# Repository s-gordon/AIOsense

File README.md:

# AIOsense

## Description
Based on the idea of an all-in-one sensor AIOsense was born.

The goal is to provide you with a sensor that is modular, affordable and
easy to solder (no SMD) as an alternative for commercially available sensors. We
also focus on upgrade-ability, so you don't have to buy all parts again in case
of a new PCB release. In most cases, this sensor is cheaper and better than the
commercially ones. 

## Available Sensors / Modules

- (RGB)-LED
- Barometer
- Breath VOC equivalent
- Buzzer / Beeper
- CO² equivalent
- Humidity sensor
- Light / Illumination sensor
- Microphone
- PIR motion sensor
- Speaker
- Temperature sensor
- Voice Assistant (ESP32-S2 / S3 only)
- mmWave / Radar sensor

All supported sensors & modules are listed in the documentation:
[Sensor Modules](https://aiosense.readthedocs.io/en/latest/sensors/)

## What does it look like? 👀

| Without lid                        | With lid                             |
|------------------------------------|--------------------------------------|
|  |  |

> **Note:** The PCB in this image is not fully equipped either is this the final case
> design ([issue](https://github.com/Schluggi/AIOsense/issues/9)).

### Rendered images

| 3D                          | 2D                       |
|-----------------------------|--------------------------|
|  |  |

### Schematic

You can find the schematic [here](schematic/AIOsense.pdf).

## Power consumption

The power consumption depends on your configuration. On a fully equipped Board (ESP32-C3 + mmWave + PIR + BME280 +
LightSensor) we measured an idle power consumption of **0.45W / 0.09A** some peaks around **0.78W / 0.15A**.

Without a mmWave sensor the idle power consumption is around **0.11W / 0.02A** and peak near **0.45W / 0.09A**.

## How to start

You want to make your own AIOsense?<br>
Let's jump right into the [documentation](https://aiosense.readthedocs.io/en/latest/quickstart/).

## Questions?

Just open an [issue](https://github.com/Schluggi/AIOsense/issues/new) :)

## Credits & Special thanks

Created and maintained by Lukas Schulte-Tickmann / [Schluggi](https://github.com/Schluggi).

### Special thanks
- My dad for some electrical engineering advice and PCB reviewing
- [lukas-holzner](https://github.com/lukas-holzner) for the case design and some general discussions about the board
- [jankae](https://github.com/jankae) for PCB reviewing
- [reschandreas](https://github.com/reschandreas) for general repo work
- [PCBWay³](https://pcbway.com/g/DFb536) for sponsoring the PCB prototypes

### Contributors

<br>

Inspired by [EverythingSmartHome](https://everythingsmarthome.co.uk/).

<hr>
³ Affiliate link

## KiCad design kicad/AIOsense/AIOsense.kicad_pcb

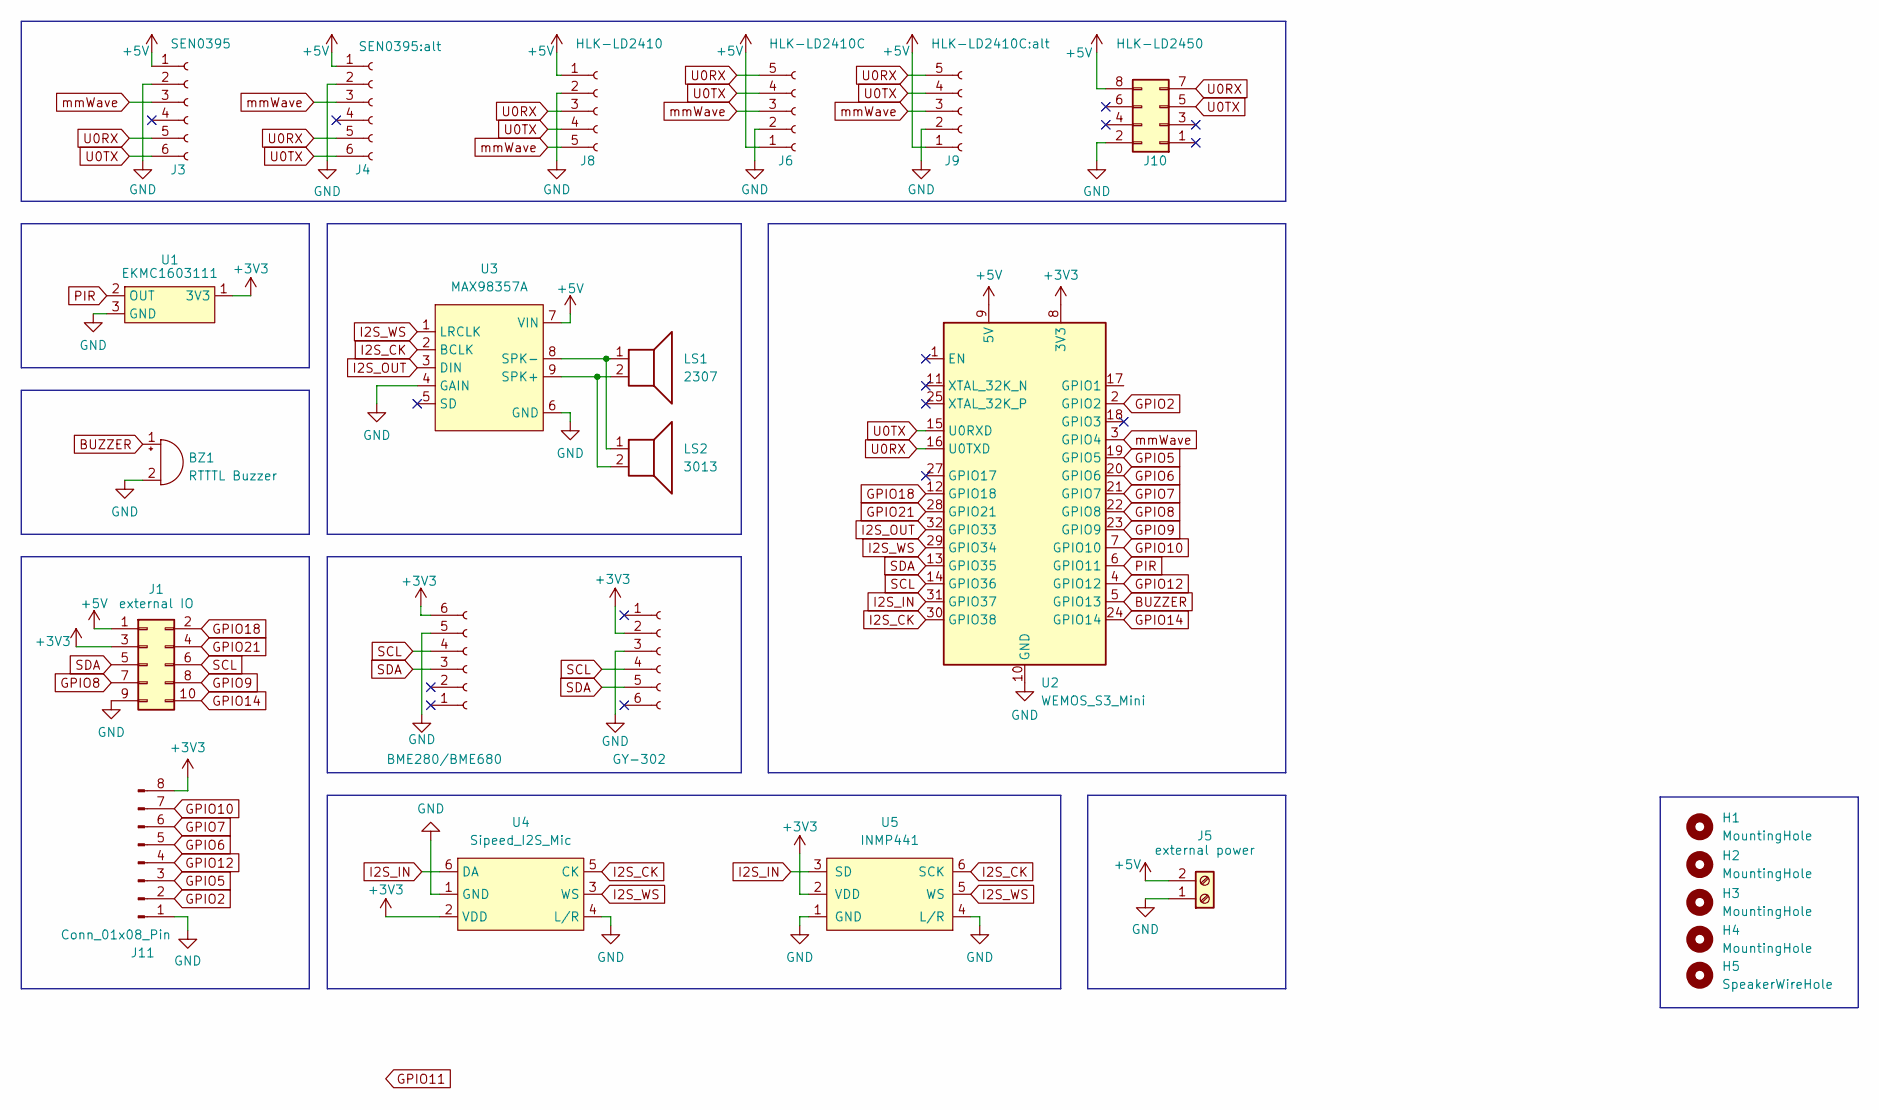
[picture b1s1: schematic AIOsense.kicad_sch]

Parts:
BZ1: RTTTL Buzzer; Buzzer_D12mm_P6.5mm
H1, H2, H3, H4: MountingHole; MountingHole_3.2mm_M3_DIN965_Pad
H5: SpeakerWireHole; Hole_Unplated_3.0mm
J1: external IO; PinHeader_2x05_P2.54mm_Vertical
J2: GY-302; PinSocket_1x06_P2.54mm_Vertical
J3: SEN0395; PinSocket_1x06_P2.54mm_Vertical; Manufacturer_Part_Number SEN0395; Digikey Part # 1738-SEN0395-ND
J4: SEN0395:alt; PinSocket_1x06_P2.54mm_Vertical; Manufacturer_Part_Number SEN0395; Digikey Part # 1738-SEN0395-ND
J5: external power; TerminalBlock_TE_282834-2_1x02_P2.54mm_Horizontal; Manufacturer_Part_Number 691210910002; Digikey Part # 732-691210910002-ND
J6: HLK-LD2410C; PinSocket_1x05_P2.54mm_Vertical; Manufacturer_Part_Number LD2410; Digikey Part # /
J7: BME280/BME680; PinSocket_1x06_P2.54mm_Vertical
J8: HLK-LD2410; PinSocket_1x05_P1.27mm_Vertical; Manufacturer_Part_Number LD2410; Digikey Part # /
J9: HLK-LD2410C:alt; PinSocket_1x05_P2.54mm_Vertical; Manufacturer_Part_Number LD2410; Digikey Part # /
J10: HLK-LD2450; PinSocket_2x04_P2.00mm_Vertical
J11: Conn_01x08_Pin; PinHeader_1x08_P2.54mm_Vertical
LS1: 2307; Speaker_2307
LS2: 3013; Speaker_3013
U1: EKMC1603111; PIR_EKMC1603111_TO-5; Manufacturer_Part_Number EKMC1603111; Digikey Part # 255-3086-ND
U2: WEMOS_S3_Mini
U3: MAX98357A; Adafruit_MAX98357A
U4: Sipeed_I2S_Mic
U5: INMP441; Manufacturer_Part_Number INMP441ACEZ-R7; Digikey Part # obsolete

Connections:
+3V3: J1.3, J2.2, J7.6, J11.8, U1.1 (3V3), U2.8 (3V3), U4.2 (VDD), U5.2 (VDD)
+5V: J1.1, J3.1, J4.1, J5.2, J6.1, J8.1, J9.1, J10.8, U2.9 (5V), U3.7 (VIN)
BUZZER: BZ1.1 (-), U2.5 (GPIO13)
GND: BZ1.2 (+), J1.9, J2.3, J3.2, J4.2, J5.1, J6.2, J7.5, J8.2, J9.2, J10.2, J11.1, U1.3 (GND), U2.10 (GND), U2.26 (GND), U3.4 (GAIN), U3.6 (GND), U4.1 (GND), U4.4 (L/R), U5.1 (GND), U5.4 (L/R)
GPIO2: J11.2, U2.2 (GPIO2)
GPIO5: J11.3, U2.19 (GPIO5)
GPIO6: J11.5, U2.20 (GPIO6)
GPIO7: J11.6, U2.21 (GPIO7)
GPIO8: J1.7, U2.22 (GPIO8)
GPIO9: J1.8, U2.23 (GPIO9)
GPIO10: J11.7, U2.7 (GPIO10)
GPIO12: J11.4, U2.4 (GPIO12)
GPIO14: J1.10, U2.24 (GPIO14)
GPIO18: J1.2, U2.12 (GPIO18)
GPIO21: J1.4, U2.28 (GPIO21)
I2S_CK: U2.30 (GPIO38), U3.2 (BCLK), U4.5 (CK), U5.6 (SCK)
I2S_IN: U2.31 (GPIO37), U4.6 (DA), U5.3 (SD)
I2S_OUT: U2.32 (GPIO33), U3.3 (DIN)
I2S_WS: U2.29 (GPIO34), U3.1 (LRCLK), U4.3 (WS), U5.5 (WS)
unnamed: LS1.2, LS2.2, U3.9 (SPK+)
unnamed: LS1.1, LS2.1, U3.8 (SPK-)
PIR: U1.2 (OUT), U2.6 (GPIO11)
SCL: J1.6, J2.4, J7.4, U2.14 (GPIO36)
SDA: J1.5, J2.5, J7.3, U2.13 (GPIO35)
U0RX: J3.5, J4.5, J6.5, J8.3, J9.5, J10.7, U2.16 (U0TXD)
U0TX: J3.6, J4.6, J6.4, J8.4, J9.4, J10.5, U2.15 (U0RXD)
mmWave: J3.3, J4.3, J6.3, J8.5, J9.3, U2.3 (GPIO4)

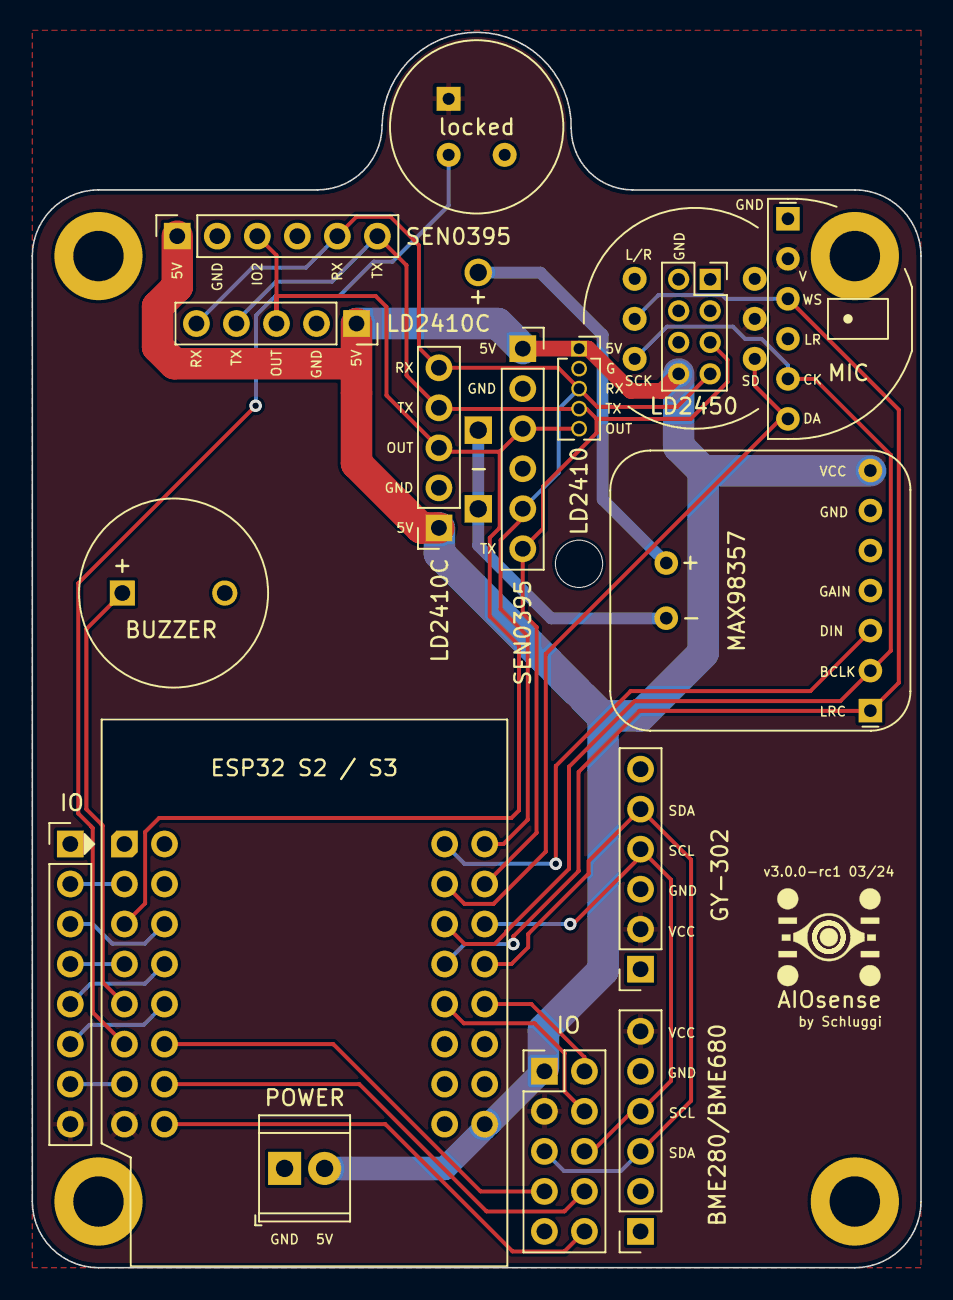
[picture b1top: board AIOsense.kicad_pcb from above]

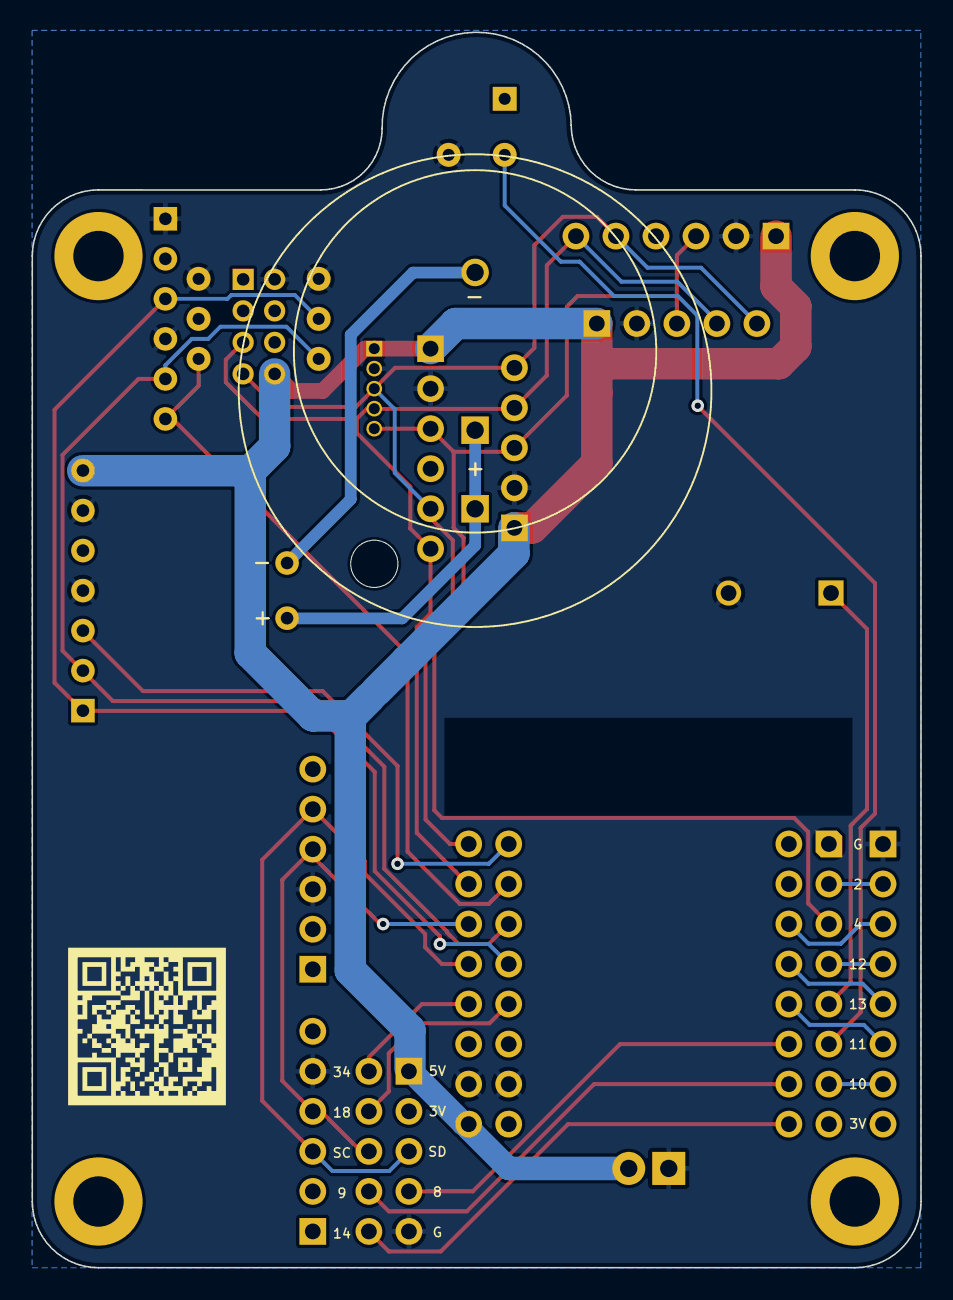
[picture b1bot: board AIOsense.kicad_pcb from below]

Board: 2 copper layers, 56.4 x 78.4 mm, 24 parts (2 on the bottom side), 27 nets.

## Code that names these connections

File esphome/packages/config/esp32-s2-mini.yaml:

substitutions:
  buzzer_pin: GPIO9
  i2s_bclk_pin: GPIO36    # SCK
  i2s_din_pin: GPIO38     # mic
  i2s_dout_pin: GPIO40    # speaker
  i2s_lrclk_pin: GPIO34   # WS
  led_pin: GPIO15
  pir_pin: GPIO11
  sen0395_io_pin: GPIO5
  uart_rx_pin: GPIO37
  uart_tx_pin: GPIO39

esp32:
  board: lolin_s2_mini
  flash_size: 4MB
  framework:
    type: esp-idf
    version: recommended

i2c:
  sda: GPIO33
  scl: GPIO35

sensor:
  - platform: internal_temperature
    name: "CPU Temperature"

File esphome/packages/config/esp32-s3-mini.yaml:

substitutions:
  buzzer_pin: GPIO13
  i2s_bclk_pin: GPIO38    # SCK
  i2s_din_pin: GPIO37     # mic
  i2s_dout_pin: GPIO33    # speaker
  i2s_lrclk_pin: GPIO34   # WS
  pir_pin: GPIO11
  rgb_led_pin: GPIO47
  rgb_led_type: RGB
  sen0395_io_pin: GPIO4
  uart_rx_pin: GPIO44
  uart_tx_pin: GPIO43

esp32:
  board: esp32-s3-devkitc-1
  variant: esp32s3
  flash_size: 4MB
  framework:
    type: esp-idf
    version: latest

i2c:
  sda: GPIO35
  scl: GPIO36
  frequency: 400kHz

sensor:
  - platform: internal_temperature
    name: "CPU Temperature"

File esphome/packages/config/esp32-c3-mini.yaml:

substitutions:
  buzzer_pin: A0
  i2s_bclk_pin: A1
  i2s_lrclk_pin: A5
  pir_pin: A4
  rgb_led_pin: GPIO7
  rgb_led_type: GRB
  sen0395_io_pin: A2
  uart_rx_pin: GPIO20
  uart_tx_pin: GPIO21

esphome:
  platformio_options:
    board_build.extra_flags:
      - "-DARDUINO_USB_CDC_ON_BOOT=0"
    board_build.flash_mode: dio

esp32:
  board: lolin_c3_mini
  flash_size: 4MB
  framework:
    type: esp-idf
    version: recommended

wifi:
  output_power: 8.5dBm

i2c:
  sda: GPIO8
  scl: GPIO10

sensor:
  - platform: internal_temperature
    name: "CPU Temperature"

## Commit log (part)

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2023-02-07 Added initial stls for case.
2023-02-07 Updated case. Light holes expanded for sensor. Made stand longer to allow clearance for USB cable. Lowered PIR sensor to proper height with TO-5 3 pin socket.
2025-01-15 Added draft VA to LED version
2025-01-15 disable led output
2025-01-15 Typo. Remove switch.is_on listen light condition for reset_led
2025-01-15 Corrected incorrect GPIO pin assignment for speaker and mic
2025-01-15 Increased trace width for amp terminals to speaker from 0.5 to 0.75 to decrease noise. Bridged GAIN to GND to increase gain from 9 dB to 12 dB
2025-01-15 Swapped GND and VDD on Sipeed mic for alt layout from vendor.
2025-01-22 Prelim updates to S3 config
2025-01-22 platform change from neopixelbus to esp32_rmt_led_strip
2025-01-22 Relaxed esp-idf version for s3
2025-01-22 Throttle LD2410
2025-01-22 Correct pin assignments for S3 mini
2025-01-22 Added speaker to VA and updated voice_assistant
2025-01-22 Remove smoothing window on BME280
2025-01-22 Added state classes
2025-01-23 Fixed esp32-s3 framework version
2025-01-23 voice assist (no-led and rgb)
2025-01-23 Removed temperature offset
2025-01-23 Removed "allow_other_uses"
2025-01-23 Brought down brightness of LED for voice assist
2025-01-24 Added vad
2025-01-24 Removed vad
2025-01-25 Added slow and fast pulse effects
2025-01-27 Added more control to switch off voice assist.
2025-01-29 Corrected renamed i2s_dout_pin for speaker.
2025-01-30 Removed obsolete boards.
2025-01-30 Updated pin assignments for rc1. Added i2s_dout_pin for amplifier/speaker.
2025-01-30 Added optional media_player sensor
2025-01-30 Added speaker to voice assist sensor. Renamed i2s component IDs to improve clarity.
2025-01-30 Removed use_wake_word switch
2025-01-30 Added wake_word_engine selector. Added micro_wake_word with alexa and hey_jarvis.
2025-01-31 Invert LED on C3 mini
2025-01-31 Corrected invert LED back and added arduino framework for C3
2025-01-31 Removed esp32 from media_player
2025-01-31 Added additional LED effects for media player announcements
2025-01-31 LED effects not supported on GPIO platform. Switched to monochromatic and ledc
2025-01-31 Update board for s2 and c3
2025-01-31 Enforce arduino frameword for media_player
2025-01-31 Switching framework in media_player is problematic
2025-01-31 Typo in platform name
2025-01-31 Added esp32 section back in to MP
2025-02-01 Added Fast Pulse and Slow Pulse light effects. Should also now set framework correctly depending on media_player and VA sensors. Added no-PSRAM config for media_player.
2025-02-01 PSRAM required
2025-02-01 On device micro wake word crashes on ESP32-S2 mini. HA only.
2025-02-01 typo
2025-02-20 Added speaker-media player introduced in 2025.2.0. ESPHome min version bumped up to 2025.2.0
2025-02-20 Added support for ESP32-S3 mini with speaker-media player. RGB light platform changes for ESP-IDF framework.
2025-02-21 Corrected led_invert from bool to str.
2025-03-08 ESPhome 2025.2 changes. Removed declaration of framework in VA instead inherit from parent config for board.
2025-03-08 Renamed i2s_audio to avoid clash with esphome. Removed ESPhome min version declaration
2025-04-24 Do not start voice assist on boot.

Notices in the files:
README.md:
License: MIT
